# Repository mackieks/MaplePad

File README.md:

# MaplePad🍁<br/>

MaplePad is an all-in-one Dreamcast controller, VMU, and Purupuru (rumble pack) emulator for Dreamcast portables and custom Dreamcast controllers. It runs on RP2040 and is usable with the Raspberry Pi Pico as well as custom MaplePad PCBs. See the [hardware folder](https://github.com/mackieks/MaplePad/tree/main/hardware) for a wiring diagram.

**Note:** MaplePad is still a WIP. You may experience issues with [Windows CE games](https://segaretro.org/Windows_CE). In almost all problematic titles, disabling VMU and rumble through the MaplePad menu will make the game playable. Check out the [Compatibility List](https://docs.google.com/spreadsheets/d/1JzTGN29Ci8SeuSGkQHLN1p6ayQNWUcsNw77SMujkjbs/edit?usp=sharing) for details!

## Features
With MaplePad you can cycle through 8 200-block internal VMUs with custom icons and colors, use an I2C or SPI OLED display to see the VMU screen in color and at 2x integer scale, and enjoy rumble that is 1:1 with the Performance TremorPak in most retail software (still some minor bugs!)

### Feature List:
- [x] Full FT<sub>0</sub> (controller) support including analog joystick and triggers
- [x] Full FT<sub>1</sub> (storage) support for savegames with 1600 blocks of space
- [x] Multipaging for memory card (8 separate 200-block memory cards)
- [x] Full FT<sub>2</sub> (LCD) support with SSD1331 96\*64 color SPI OLED for VMU display (monochrome SSD1306 128\*64 I2C OLED also supported)
- [x] Customizable color palettes for all 8 internal memory cards
- [x] Robust FT<sub>8</sub> (vibration) functionality (WIP)
- [x] Robust FT<sub>3</sub> (timer/RTC) reporting for compatibility purposes (no RTC)
- [x] Basic menu on SSD1306 and SSD1331 OLED for configuring MaplePad behavior (WIP)

### To-do: 
Release v1.6 is gated by the following TODOs
- [ ] Finish menu (button test, VMU palette editor, misc. bugs)
- [ ] Address issues with non-CE games (Crazy Taxi, Blue Stinger, Powerstone 2)
- [ ] Finish FT<sub>8</sub> (vibration) continuous vibration and AST

Future TODOs
- [ ] Fix compatibility with Windows CE games
- [ ] Implement 'fancy' VMU color palettes (gradients, animated backgrounds, etc.)
- [ ] Implement option for DC boot animation on OLED
- [ ] Add external RTC for true FT<sub>3</sub> (timer/RTC) support
- [ ] Implement FT<sub>4</sub> (microphone) support

## Project Showcase
*StrikerDC MaplePad mod by Wesk*

*MaplePad Arcade Controller with VMU de GamesCare. [link](https://gamescare.com.br/produto/controle-arcade-dreamcast-tela-de-vmu-e-8-vmus-virtuais-na-placa-maple-board/), [video](https://www.youtube.com/watch?v=b0IbSASR3B4/)*

*Mini Arcade Stick de Mundo Yakara Colombia. Excellent video that showcases MaplePad v1.5 features! [video](https://www.youtube.com/watch?v=jbHO3rEyzZU)*

*Mini plug'n'play virtual memory card by jounge. [link](https://tieba.baidu.com/p/8465994390)*

*Various JAMMA Dreamcast adapters available on AliExpress. [link 1](https://www.aliexpress.us/item/3256805216279752.html), [link 2](https://www.aliexpress.us/item/3256804674679708.html), [video](https://www.youtube.com/shorts/UciW3vM-KWo) (flashing lights warning!)*

*Giant Dreamcast VMU + Arcade Stick by CrazyJojo (code modified). [video](https://www.youtube.com/watch?v=bEA_On7P_g8)*

## Dumping VMUs to PC
You can use [picotool](https://github.com/raspberrypi/picotool) to dump VMUs manually. Here's the process:

- Put RP2040 into programming mode with BOOTSEL button and connect it to your PC
- Use picotool to dump whichever VMU page you want: `picotool save -r 10020000 10040000 dump1.bin`

- VMUs start at 0x10020000 and each one is 0x20000 long. So to save page 7, for example, you'd use 
`picotool save -r 100E0000 10100000 dump7.bin`
- Open dump in [VMU Explorer](https://segaretro.org/VMU_Explorer)

## License
<br />This work is licensed under a <a rel="license" href="http://creativecommons.org/licenses/by/4.0/">Creative Commons Attribution 4.0 International License</a>.

Share — copy and redistribute the material in any medium or format <br />
Adapt — remix, transform, and build upon the material for any purpose, even commercially. <br />
Attribution — You must give appropriate credit, provide a link to the license, and indicate if changes were made. <br />

MaplePad is forked from [Charlie Cole's Pop'n Music Controller.](https://github.com/charcole/Dreamcast-PopnMusic)

Special thanks: [Charlie Cole](https://github.com/charcole), [Colton Pawielski](https://github.com/cepawiel) and [Wesk](https://www.youtube.com/channel/UCYAwbbBxi5_LK8WVrD10SUw).

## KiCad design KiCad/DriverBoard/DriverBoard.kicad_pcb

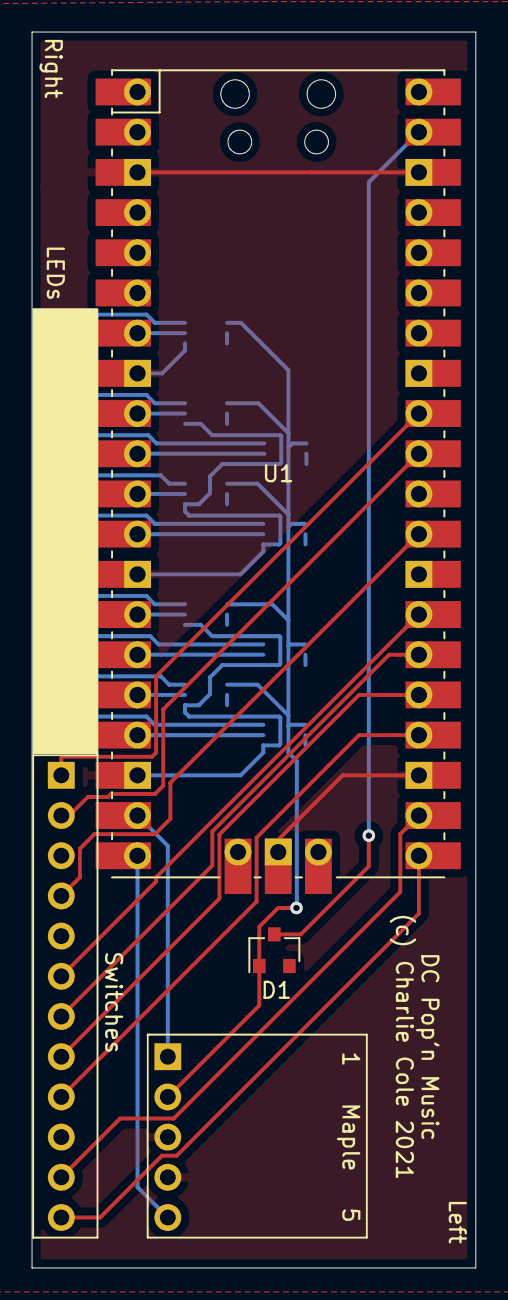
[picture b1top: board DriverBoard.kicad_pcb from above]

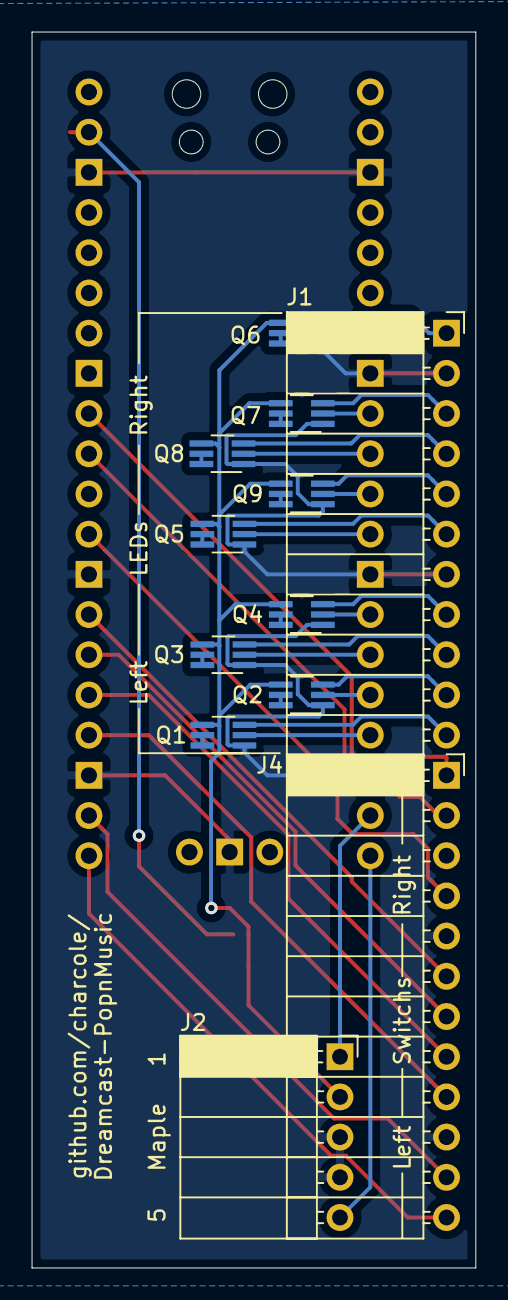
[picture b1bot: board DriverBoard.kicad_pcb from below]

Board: 2 copper layers, 28.0 x 78.1 mm, 14 parts (12 on the bottom side), 41 nets.

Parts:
D1: D_Schottky; D_SOT-23_ANK
J1: Conn_01x11; PinSocket_1x11_P2.54mm_Horizontal
J2: Conn_01x05; PinSocket_1x05_P2.54mm_Horizontal
J4: Conn_01x12; PinSocket_1x12_P2.54mm_Horizontal
Q1, Q2, Q3, Q4, Q5, Q6, Q7, Q8, Q9: Q_DUAL_NPN_PNP_BRT_E1B1C2E2B2C1; SOT-363_SC-70-6_Handsoldering
U1: Pico; RPi_Pico_SMD_TH

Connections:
+5V: D1.2, J2.2, Q1.4, Q2.4, Q3.4, Q4.4, Q5.4, Q6.4, Q7.4, Q8.4, Q9.4
GND: J1.2, J1.7, J2.3, J2.4, J4.5, J4.10, Q1.1, Q2.1, Q3.1, Q4.1, Q5.1, Q6.1, Q7.1, Q8.1, Q9.1, U1.3, U1.8, U1.13, U1.18, U1.23, U1.28, U1.38, U1.42
LED_LEFT_BLUE: Q4.2, U1.14
LED_LEFT_BLUE_5V: J1.8, Q4.3
LED_LEFT_GREEN: Q3.2, U1.15
LED_LEFT_GREEN_5V: J1.9, Q3.3
LED_LEFT_WHITE: Q1.2, U1.17
LED_LEFT_WHITE_5V: J1.11, Q1.3
LED_LEFT_YELLOW: Q2.2, U1.16
LED_LEFT_YELLOW_5V: J1.10, Q2.3
LED_MIDDLE_RED: Q5.2, U1.12
LED_MIDDLE_RED_5V: J1.6, Q5.3
LED_RIGHT_BLUE: Q9.2, U1.11
LED_RIGHT_BLUE_5V: J1.5, Q9.3
LED_RIGHT_GREEN: Q8.2, U1.10
LED_RIGHT_GREEN_5V: J1.4, Q8.3
LED_RIGHT_WHITE: Q6.2, U1.7
LED_RIGHT_WHITE_5V: J1.1, Q6.3
LED_RIGHT_YELLOW: Q7.2, U1.9
LED_RIGHT_YELLOW_5V: J1.3, Q7.3
MAPLE_PIN1: J2.1, U1.19
MAPLE_PIN5: J2.5, U1.20
unnamed: D1.1, U1.39
unnamed: Q1.5, Q1.6
unnamed: Q2.5, Q2.6
unnamed: Q3.5, Q3.6
unnamed: Q4.5, Q4.6
unnamed: Q5.5, Q5.6
unnamed: Q6.5, Q6.6
unnamed: Q7.5, Q7.6
unnamed: Q8.5, Q8.6
unnamed: Q9.5, Q9.6
SW_LEFT_BLUE: J4.8, U1.25
SW_LEFT_GREEN: J4.9, U1.24
SW_LEFT_WHITE: J4.12, U1.21
SW_LEFT_YELLOW: J4.11, U1.22
SW_MIDDLE_RED: J4.7, U1.26
SW_RIGHT_BLUE: J4.6, U1.27
SW_RIGHT_GREEN: J4.4, U1.29
SW_RIGHT_WHITE: J4.1, U1.32
SW_RIGHT_YELLOW: J4.2, U1.31

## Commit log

2021-01-31 Working Maple input
2021-02-01 Working controller emulation
2021-02-07 Buttons and LEDs but bad packets are back
2021-02-07 PIO code golf
2021-02-12 New faster decoding (untested)
2021-02-12 Cache built packets for faster sending
2021-02-13 Some fast recieve bug fixing
2021-02-13 Working!
2021-02-13 Removed unused code now working
2021-02-14 Tidied up and commented ready for release
2021-02-14 Moved state machine into own file
2021-02-14 Comment and tidy ready for release
2021-02-14 Fixed typo
2021-02-14 Far too long README that no-one will ever read
2021-02-14 Add VSCode config files
2021-02-14 Added photos and design files
2021-02-14 Added link to photos and fixed some errors
2021-02-14 Added license
2021-02-14 Improved README
2021-02-14 Tweaked README
2021-02-14 Added Fusion 360 screenshot
2021-02-16 Fixed typos
2021-02-21 Initialize TXDMAChannel properly
2021-02-27 Memory card support
2021-02-28 Working memory card support
2021-02-28 Commented odd behaviour
2021-02-28 Memory card fixes
2021-03-02 Preformat memory card with custom icon
2021-03-02 Update flash offset to force reformat of memory card
2021-03-02 Add more information about memory card functionality
2021-03-06 Support being plugged in on any port
2021-03-06 First attempt at controller board that fits in PCB slot
2021-03-06 Added 5V LED drivers
2021-03-20 Switched misleading silkscreen and updated part numbers
2021-03-20 Added some info about PCB
2021-08-19 Addition of analog stick
2021-08-30 FT2: I2C LCD
    Added:
    -Monochrome LCD (FT2) with SSD1306 128*64 I2C OLED for VMU display
    -Analog Triggers
    -Basic Timer (FT3) reporting; Timer packets not yet implemented
2021-09-04 MaplePad Hardware Update
    -Updated pin assignments in maple.c for MaplePad
    -Gerbers and BOM for MaplePad PCB added
    -Preliminary dual subperipheral support added
    -Preliminary FT8 (vibration) packet format
2021-09-04 Rename Hardware.MD to README.MD
2021-09-05 Multipaging Update
    -Added multipaging to FT1 Storage functionality
    -8 separate 200-block memory cards
    -Interrupt-driven page cycling using pushbutton
    Misc:
    -Toned down overclock to mitigate instability (now 200MHz)
2021-09-05 Page Button Fix
    -Added 750ms page cycle debounce delay
    -Initial support for 128*64 OLED testing
2021-11-20 spi color oled in progress
2021-11-21 Custom palettes for SPI OLED
2022-02-01 WIP Rumble Implementation
    -Purupuru functionality (WIP)
    -Color SPI OLED tweaks
    ...and probably more I've forgotten!
2022-07-12 Initial Purupuru Support
    Added basic vibe handling code. Still many many things to implement
2022-07-12 Add MaplePad PCB image
2022-07-12 MaplePad HW Files
    -EAGLE schematic and board
    -Gerbers
    -BOM
    -Assembly drawing
2022-07-12 Add maplepad_pcb.jpg
2022-07-12 Update HW stuff
2022-07-12 Add maplepad_logo.png
2022-07-15 Fix profile.gbr
2022-07-15 working on Pico/MaplePad support
2022-07-15 Rename Icon/Icon.c to icon/Icon.c
2022-07-15 Revert "Rename Icon/Icon.c to icon/Icon.c"
    This reverts commit 7aa6d986047386498e97657ecb66427d15105bdc.
2022-07-15 Working on HKT-7300 support
2022-07-17 Fix format.c
2022-07-17 Remove build/
2022-07-20 vibeHandler floats
2022-07-28 Purupuru Updates
    -Basic and incremented purupuru pulses working
    -New logo
2022-07-31 PuruPuru and FT2 DMA Update
    Massive update:
    -Vibration handling is almost feature-complete, including incrementing pulses, convergent and divergent vibration, and auto-stop time framework.
    -SSD1331 OLED now uses DMA instead of blocking SPI
    -Optional button combo (X + Y + Start) to activate VMU page cycle
    -Tweaks to rumble GPIO settings
2022-08-04 Memory card format and rumble hotfix
2022-08-08 VMU improvements, rumble fixes, bug squashin'
    -Filesystem tweaks to increase data area to 238 blocks per page
    -Rate-limited button combo VMU page cycling
    -Fixed vibeHandler timer settings to improve accuracy
    -Fixed incorrect handling of Purupuru commands when vibePower = 0
    -Increased flash_write_delay to improve reliability
    -Custom palettes in Dreamcast BIOS for memory cards
2022-08-15 Packet format updates
    Various bugfixes for issues found while troubleshooting Sega Rally 2, mostly packet formatting stuff
    Revert to 200 block memcards to avoid issues when copying in BIOS
2022-08-16 WIP stuff
    -forward and backward vmu cycling
    -persistent vmu pages
2022-08-18 menu updates
2022-08-18 FT3 Timer Initial Support
    ft3 data structures, command handling, block_read bugfixes
2022-09-19 Menu updates, packet data fixes, cleanup
2022-09-19 remove stdio_usb (oops)
2022-09-19 rearrange images
2022-09-19 add strikerDC images
2022-09-30 added wiring diagram!
2022-10-16 Fix Extended Device Info fields
    -fixed arcade stick free device status
    -fixed arcade stick power consumption
    -updated standard controller free device status to more recent HKT-7700 revision
2022-10-19 move drawing funcs to draw.c
    Prep for bringing back full ssd1306 support (menu+vmu)
2022-10-20 display.c
    reorganizing
2022-10-20 move LICENSE
2022-10-20 oledType fixes
    mono OLED fixes (WIP)
2022-10-21 SSD1306 OLED Support
    Monochrome I2C SSD1306 OLED support now working! Also you can swap L&R triggers or X&Y axes in the menu now.
    plus some random bugfixes for the menu flags
2022-10-21 Update LICENSE
2022-12-10 1.4d update
2023-01-09 Update maple.c
    Fix firstboot vmu formatting issue
2023-02-21 Working on menu + new stick config
2023-02-23 Ellipse fill and button test screen
2023-02-23 tweaking stick deadzone/calib stuff
2023-02-23 Working on antideadzone
2023-04-05 Update maple.c
    reverting WIP antideadzone stuff; more important stuff to work on right now
2023-04-13 revert old wip stuff
2023-04-14 update sCal, iconData
    -fix stick calibration wizard
    -remove extra icon data
2023-04-14 wip stuff
    -trying to remove outer stick deadzone
    -working on hiding menu entries for ssd1306
2023-04-14 deadzone work
    -tweaked stick/trigger calibration
    -working on deadzone adjustment menus
2023-04-14 formatting
2023-04-15 update menu, scal/tcal
    -remove janky entry hiding
    -implement deadzone adjust menus for stick/triggers
    -formatting
2023-11-29 arcade soft reset wip
    working on new lcd support, soft reset for arcade cab
2023-12-04 maplepad v1.5
    -hugely improved stick calibration (fully automatic)
    -deadzone and anti-deadzone adjustment for stick and triggers
    -autoreset with configurable timer and inter-maplepad communication for arcade cabinets
    -optimized display pixel-setting functions (reduces controller disconnects during saving)
    -fixed ssd1306 clearDisplay bug
    -added Settings menu controller type indicator
2024-01-23 Create HW_LICENSE.txt
    solderpad license for hw
2024-11-11 init check-in, staging for refactoring
2024-11-12 added gpios and changed maplebus pins
2024-11-13 setup callback for vmu to only update flash when storage is written to
2024-11-15 removing remnants of usb now that I understand how the communications work. TODO update IO within DreamcastController
2024-11-15 missed removing a subdirectory
2024-11-15 implemented gpio for button presses and injected it into the DreamcastController handlePacket() method
2024-11-16 removing checked in build cache files
2024-11-16 fixed compiler issues
2024-11-20 Added adc reads for trigger + joystick inputs
2024-11-20 organizing for screen implementation
2024-11-20 added to cmake before I forget
2024-11-21 configured oled 1331 and displayed splashscreen
2024-11-25 enabling uart for debugging
2024-11-26 screen now updates with maple packets, need to fix display rendering
2024-11-28 fixed screen artifacting and added 2x integer scaling. this code is tech debt and is in desperate need of refactoring/optimization
2024-11-28 some code cleanup
2024-11-28 figure out why the pointer to lcd is too slow an causing the controller to pause
2024-11-29 improved lcd implementation for performance
2024-11-30 resolved screen update issues
2024-11-30 small optimization
2024-12-01 please don't judge me for the poor font implementation
2024-12-02 cleaned up fonts
2024-12-02 beginning to integrate menu system
2024-12-06 setup framework for menu system
2024-12-11 updated to 2.1 pico sdk
2024-12-12 updated menu with cursor and scrolling
2024-12-12 some refactoring
2024-12-13 menu improvements
2024-12-14 updates to how memory is handled to allow for paging
2024-12-17 push everything
2024-12-17 fix for oled sel
2024-12-18 cleaned up paging and stabilized it
2024-12-18 some minor refactoring for paging
2024-12-18 added logic to detect uart to swap A and B buttons
2024-12-29 minor refactoring and plumbing for observers
2024-12-30 observer pattern is 'working'
2025-01-02 these changes are going to be reverted
2025-01-02 reverting to previous commit
2025-01-02 resolved previous commit issues where screen logic was too slow causing the controller to crash
2025-01-03 need to figure out how to save memory for buffers
2025-01-07 Added logic to handle an overlay that appears for 2 seconds then goes back to displaying content on the screen
2025-01-08 modified the overlay so that it only takes a portion of the top screen, leaving the rest of the content to be rendered as normal
2025-01-10 lots of overlay updates
2025-01-10 addressed oom issues, probably created more headaches for future me
2025-01-11 extreme hoarders, static variable cleanup edition
2025-01-12 It pains me to have to implement fonts this way, but hashtables were proving to be too hard on memory
2025-01-14 fully expecting to have to revert back to a previous commit with these changes.
2025-01-15 these changes will be reverted
2025-01-15 Revert "these changes will be reverted"
    This reverts commit 13d6e20f658a472039c56de2295e74f7eeeab584.
2025-01-15 Revert "fully expecting to have to revert back to a previous commit with these changes."
    This reverts commit f9f0f88d52b299bf84395fcb49b3441ae3920cd0.
2025-01-15 Revert "It pains me to have to implement fonts this way, but hashtables were proving to be too hard on memory"
    This reverts commit cd45ddc3e47e3ec0241de3ceff5dc994dd6091fc.
2025-01-15 reverted changes
2025-01-15 changed compile settings to run Os (size) optimization to fix memory issues, thanks Tails!
2025-01-16 Broke menu out into it's own subdirectory
2025-01-29 implemented reading flash for storing settings data, next up storing it
2025-01-31 settings saving, will do some refactoring to make it cleaner
2025-01-31 oops, forgot to cleanup some stuff before committing
2025-01-31 happier with this memory approach to saving settings data
2025-02-01 more menu work, it's getting there!
2025-02-03 settings persisting and startup check created to set defaults when firmware is upgraded
2025-02-04 controller now uses configurations updated in settings
2025-02-04 bug squishing
2025-02-05 resolved a lot of issues
2025-02-05 more bug fixes
2025-02-06 removed need for pulling in sdk as submodule, pico sdk should now be cloned locally from the master branch
2025-02-07 updated for Pico2
2025-03-08 Rename 主机演示2[00_05_12][20221030-111434].png to jojo1
2025-03-08 Rename jojo1 to jojo1.png
2025-03-08 Rename images/从机演示2生化[00_08_05][20221030-111628].png to jojo2.png
2025-03-08 Rename 从机演示4[00_01_19][20221030-111601].png to jojo3.png
2025-03-08 Rename jojo2.png to images/jojo2.png
